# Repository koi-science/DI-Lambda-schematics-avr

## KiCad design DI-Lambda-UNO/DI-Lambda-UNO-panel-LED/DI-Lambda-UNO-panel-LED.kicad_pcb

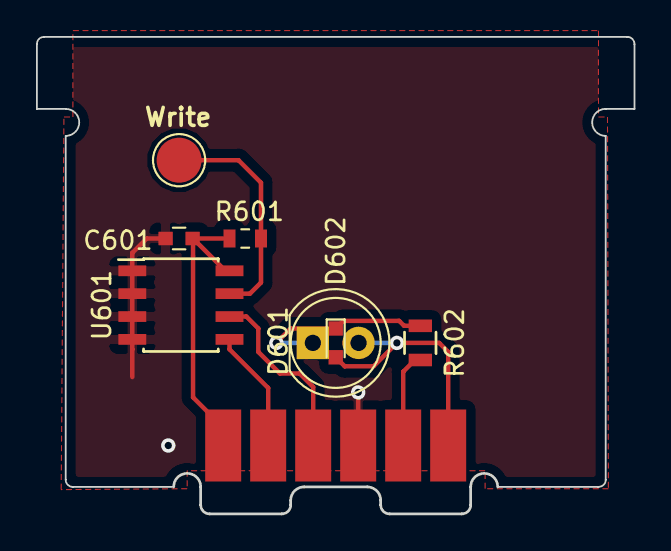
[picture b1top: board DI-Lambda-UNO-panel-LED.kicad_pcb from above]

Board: 2 copper layers, 33.2 x 26.5 mm, 9 parts (0 on the bottom side), 8 nets.

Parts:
C601: 0.1uF 25v; C_0603
D601: LED; LED_D5.0mm
D602: LED; LED_0603
J601: Conn_01X06; Contact-2.5x6
MK601: Mounting_Hole; Tab_LED
R601: 4.75K; R_0603_1608Metric
R602: 470R; R_0805
U601: 24LC02; SOIC-8_3.9x4.9mm_Pitch1.27mm
W601: WRITE; TestPoint_Pad_D2.5mm

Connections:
/GLED: J601.5, R602.1
/SCL: J601.3, U601.6
/SDA: J601.2, U601.5
/VCC: C601.1, J601.1, R601.1, U601.8
/VLED: D601.2, D602.2, J601.6
GND: C601.2, J601.4, U601.1, U601.2, U601.3, U601.4
unnamed: D601.1, D602.1, R602.2
unnamed: R601.2, U601.7, W601.1

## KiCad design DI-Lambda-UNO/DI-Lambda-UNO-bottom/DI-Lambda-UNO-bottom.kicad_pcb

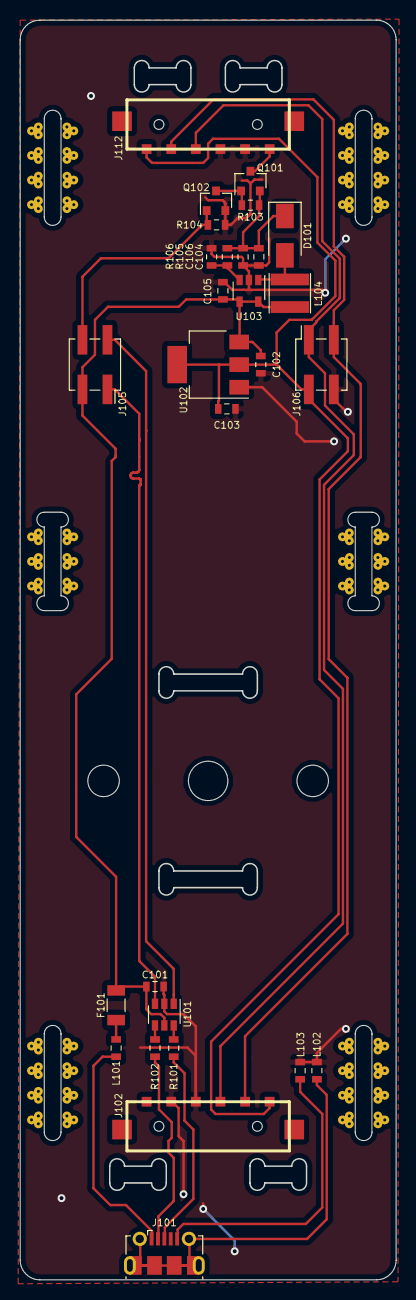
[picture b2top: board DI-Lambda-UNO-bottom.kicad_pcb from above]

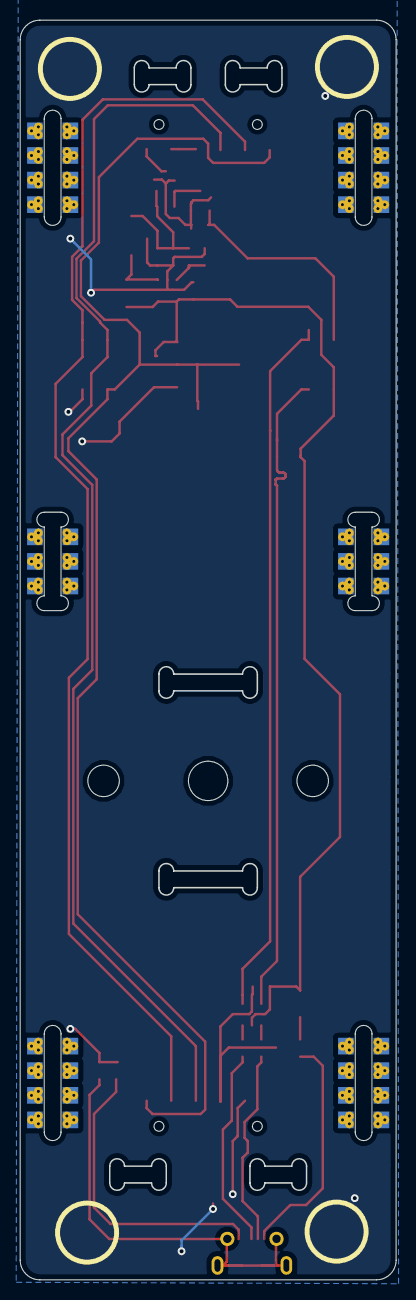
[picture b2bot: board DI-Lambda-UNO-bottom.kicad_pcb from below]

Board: 2 copper layers, 38.2 x 128.0 mm, 39 parts (6 on the bottom side), 21 nets.

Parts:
C101, C102, C103, C105: 4.7uF 6.3v; C_0603_1608Metric
C104, C106: 1uF 16v; C_0603_1608Metric
D101: SS14; D_SMA
F101: 0.2A; Fuse_1206_3216Metric
J101: USB_OTG; USB_Micro-B_Molex-105017-0001
J102, J112: CONN_01X06; Spring-contact-connector-2.5x6
J103, J104, J110, J111: Conn_02x04_Odd_Even; Pocket_1.6mm_10mm_no_cap_8pads_short_vias
J105, J106: Conn_02x02_Odd_Even; PinSocket_2x02_P2.54mm_Vertical_SMD
J107: Conn_01x01; Cuvette-holder
J108, J109: Conn_02x03_Odd_Even; Pocket_1.6mm_10mm_2cap_6pads_short_vias
L101, L102, L103: FB; L_0603_1608Metric
L104: 6.8uH; L_Taiyo-Yuden_NR-40xx
MK101: Mounting_Hole; Slot_LED
MK102, MK103: Mounting_Hole; Slot_pinhole
MK104: Mounting_Hole; Slot_sensor
Q101: AO3401; SOT-23
Q102: AO3400; SOT-23
R101, R102: 22R; R_0603_1608Metric
R103, R104, R106: 4.75k; R_0603_1608Metric
R105: 42.2k; R_0603_1608Metric
U101: USBLC6-2SC6; SOT-23-6
U102: 3.3v LDO; SOT-223-3_TabPin2
U103: AP3015; SOT-23-5

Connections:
/12v: C104.1, C106.1, D101.1, Q101.2, R103.1, R105.1
/DI_N: J101.2, R102.2
/DI_P: J101.3, R101.2
/D_N: J105.1, U101.3
/D_P: J105.2, U101.1
/LED_PWM: J105.4, Q102.1, R104.1
/SCL: J102.3, J106.1, J112.3
/SDA: J102.2, J106.3, J112.2
/SW: D101.2, L104.1, U103.1
/VBUS: C101.1, C102.2, C105.2, F101.1, J105.3, L104.2, U101.5, U102.3, U103.4, U103.5
/VCC: C103.2, J102.1, J106.2, J112.1, U102.2
/VLED: J112.6, Q101.3
/_D_N: R102.1, U101.4
/_D_P: R101.1, U101.6
GND: C101.2, C102.1, C103.1, C104.2, C105.1, C106.2, J102.4, J102.5, J106.4, J112.4, J112.5, L102.2, L103.2, Q102.2, R104.2, R106.2, U101.2, U102.1, U103.2
unnamed: F101.2, L101.1
unnamed: J101.1, L101.2
unnamed: J101.5, L103.1
unnamed: J101.6, L102.1
unnamed: Q101.1, Q102.3, R103.2
unnamed: R105.2, R106.1, U103.3

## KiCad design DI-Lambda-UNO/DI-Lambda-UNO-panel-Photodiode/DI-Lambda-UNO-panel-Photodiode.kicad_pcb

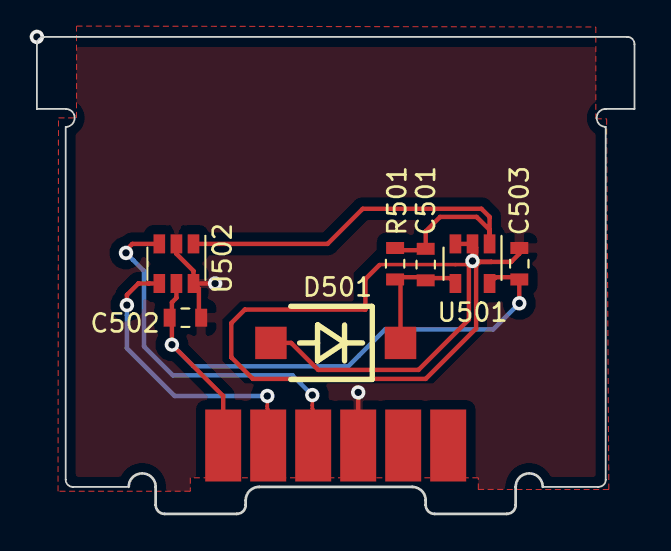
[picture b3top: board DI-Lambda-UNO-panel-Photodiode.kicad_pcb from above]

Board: 2 copper layers, 33.2 x 26.5 mm, 9 parts (0 on the bottom side), 6 nets.

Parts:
C501: 10pf; C_0603_1608Metric
C502, C503: 0.1uF 25v; C_0603_1608Metric
D501: D_Photo; 2-SMD-Everlight-Photodiode
J501: Conn_01X06; Contact-2.5x6
MK501: Mounting_Hole; Tab_SENSOR
R501: 1M; R_0603_1608Metric
U501: TP1271; SOT-23-5
U502: MCP3421A0T-E/CH; SOT-23-6

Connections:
/SCL: J501.3, U502.3
/SDA: J501.2, U502.4
/VCC: C502.1, C503.1, J501.1, U501.5, U502.5
GND: C502.2, C503.2, D501.2, J501.4, U501.2, U501.3, U502.2, U502.6
unnamed: C501.1, R501.1, U501.1, U502.1
unnamed: C501.2, D501.1, R501.2, U501.4

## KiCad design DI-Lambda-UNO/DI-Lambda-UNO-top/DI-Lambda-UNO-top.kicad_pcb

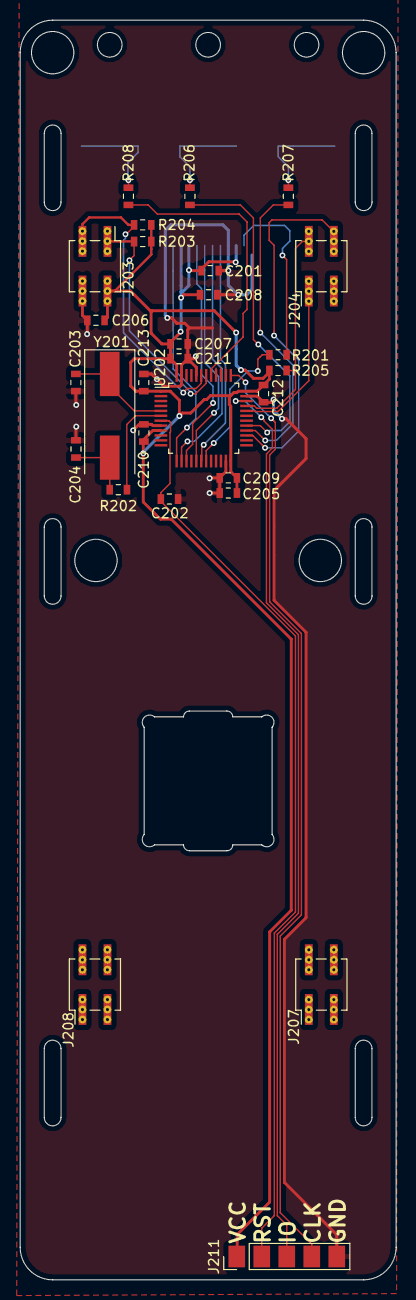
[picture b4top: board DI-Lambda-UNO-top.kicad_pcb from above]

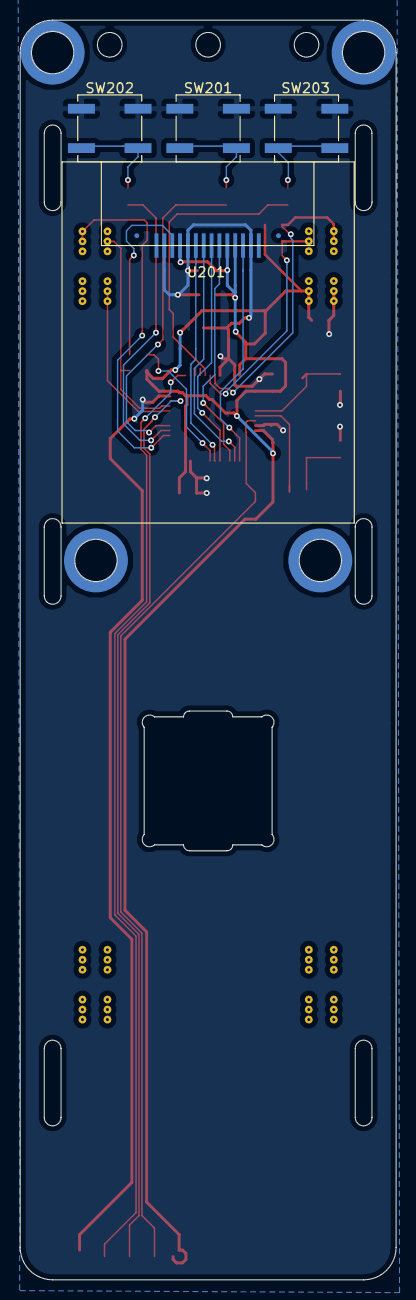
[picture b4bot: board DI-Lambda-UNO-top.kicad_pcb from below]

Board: 2 copper layers, 38.2 x 128.0 mm, 44 parts (14 on the bottom side), 26 nets.

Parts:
C201, C205, C206, C207: 4.7uF 6.3v; C_0603_1608Metric
C202, C208, C209, C210, C211, C212, C213: 0.1uF 25v; C_0603_1608Metric
C203, C204: 10pF 25V; C_0603_1608Metric
J201, J202, J209, J210: Conn_02x04_Odd_Even; Pocket_1.6mm_7mm_no_cap
J203, J204, J207, J208: Conn_02x02_Odd_Even; PinHeader_2x02_P2.54mm_Vertical_SMD_vias
J205, J206: Conn_02x03_Odd_Even; Pocket_1.6mm_7mm_no_cap
J211: Conn_01x05; Testpoint_1x05_P2.54mm_mixed
MK201: Mounting_Hole; Button_mounts_x3
MK202, MK203, MK204, MK205: Mounting_Hole; Mounting-Hole-SMT-nut-M3-4.3mm
MK206: Mounting_Hole; Cuvette-cutout-top
R201: 220R; R_0603_1608Metric
R202: 390R; R_0603_1608Metric
R203, R204: 4.75K; R_0603_1608Metric
R205, R206, R207, R208: 1.5K; R_0603_1608Metric
SW201: SW_SAMPLE; SW_SPST_B3SL-1002P
SW202: SW_MODE; SW_SPST_B3SL-1002P
SW203: SW_BLANK; SW_SPST_B3SL-1002P
U201: LCD_1.44_ST7735
U202: STM32F103C8Tx; LQFP-48_7x7mm_P0.5mm
Y201: 8Mhz; Crystal_SMD_HC49-SD

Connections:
/BLANK: R208.2, U202.41
/DN: J204.1, U202.32
/DP: J204.2, R205.2, U202.33
/LCD_A0: U201.7, U202.14
/LCD_CS: U201.12, U202.13
/LCD_LED: R201.2, U202.19
/LCD_RST: U201.6, U202.18
/LED_PWM: J204.4, U202.27
/MODE: R207.2, U202.28
/MOSI: U201.8, U202.17
/SAMPLE: R206.2, U202.29
/SCK: U201.9, U202.15
/SCL: J203.1, R203.2, U202.42
/SDA: J203.3, R204.1, U202.43
/SWDCLK: J211.4, U202.37
/SWDIO: J211.3, U202.34
/VCC: C201.2, C205.2, C206.2, C207.2, C208.1, C209.1, C210.1, C211.1, C212.1, C213.1, J203.2, J211.1, R203.1, R204.2, R205.1, U201.4, U201.10, U201.11, U202.1, U202.9, U202.24, U202.36, U202.48
/nRST: C202.1, J211.2, U202.7
GND: C201.1, C202.2, C203.2, C204.2, C205.1, C206.1, C207.1, C208.2, C209.2, C210.2, C211.2, C212.2, C213.2, J203.4, J211.5, SW201.2, SW202.2, SW203.2, U201.2, U201.5, U201.13, U202.8, U202.23, U202.35, U202.44, U202.47
unnamed: C203.1, U202.5, Y201.1
unnamed: C204.1, R202.2, Y201.2
unnamed: R201.1, U201.3
unnamed: R202.1, U202.6
unnamed: R206.1, SW201.1
unnamed: R207.1, SW202.1
unnamed: R208.1, SW203.1

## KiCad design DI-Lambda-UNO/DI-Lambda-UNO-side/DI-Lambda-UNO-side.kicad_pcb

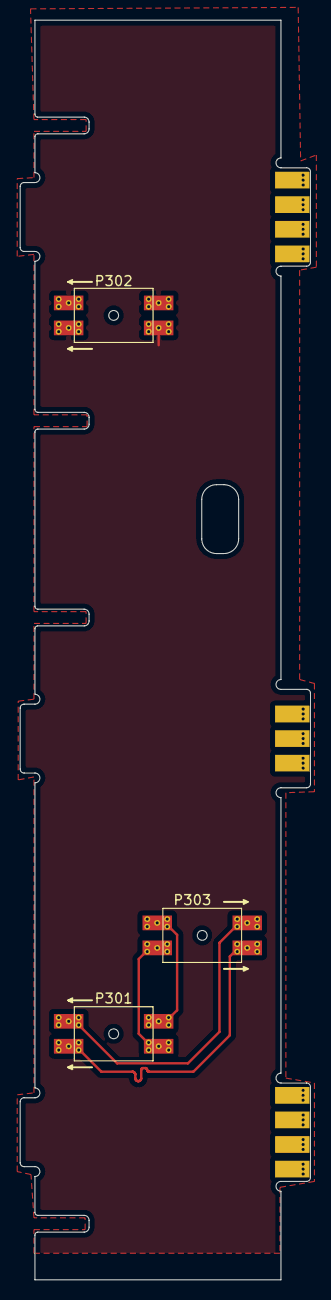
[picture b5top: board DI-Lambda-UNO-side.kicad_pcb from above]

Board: 2 copper layers, 29.5 x 128.0 mm, 10 parts (0 on the bottom side), 5 nets.

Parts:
MK301, MK302, MK303: Mounting_Hole; Tab_7mm_1.5mm
MK304: Mounting_Hole; Cuvette_holder_side_hole
P301, P302, P303: CONN_02X02; Female_socket_2.54_2x2p_horizontal_smt
P304, P306: CONN_01X04; Tab_10mm_4pads_vias_3mm
P305: CONN_01X04; Tab_10mm_3pads_vias_3mm

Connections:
/A+: P301.1, P303.3
/A-: P301.3, P303.1
/B+: P301.4, P303.2
/B-: P301.2, P303.4
GND: P302.1, P302.2, P302.3, P302.4

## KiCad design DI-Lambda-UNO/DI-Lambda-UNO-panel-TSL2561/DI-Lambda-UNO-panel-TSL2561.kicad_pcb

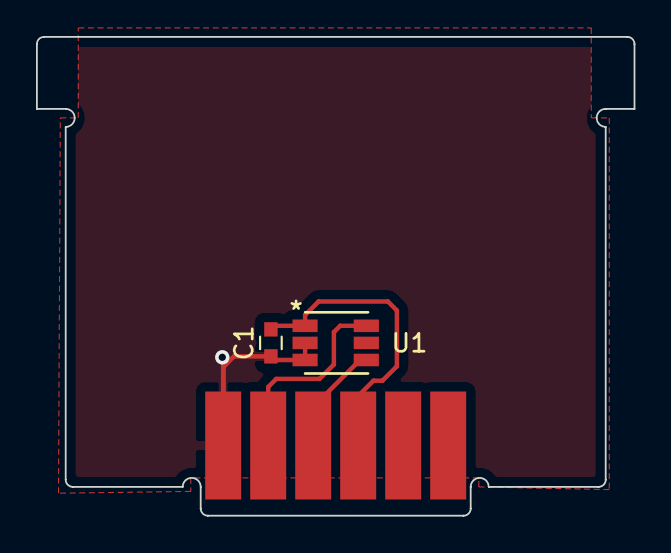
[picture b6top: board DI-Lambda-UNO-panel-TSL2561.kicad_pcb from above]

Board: 2 copper layers, 33.2 x 26.6 mm, 3 parts (0 on the bottom side), 4 nets.

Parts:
C1: C_Small; C_0603
J1: Conn_01X06; Contact-2.5x6
U1: TSL2561; TMB-6

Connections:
/SCL: J1.3, U1.4
/SDA: J1.2, U1.6
/VCC: C1.1, J1.4, U1.1
GND: C1.2, J1.1, U1.2, U1.3

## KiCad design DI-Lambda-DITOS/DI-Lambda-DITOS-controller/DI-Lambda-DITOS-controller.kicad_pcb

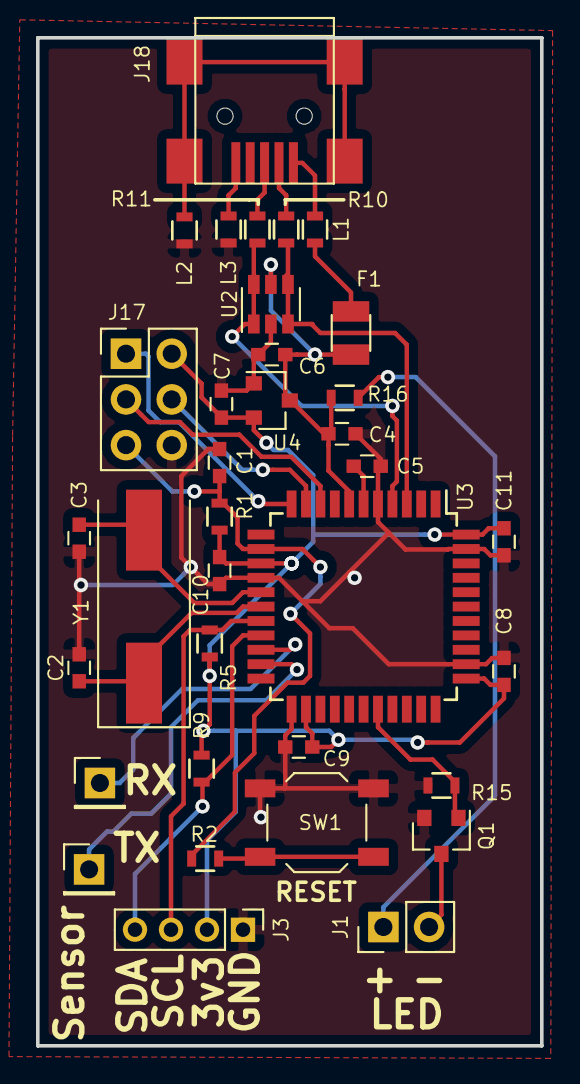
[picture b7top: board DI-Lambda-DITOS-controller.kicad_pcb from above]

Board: 2 copper layers, 28.0 x 56.0 mm, 35 parts (0 on the bottom side), 26 nets.

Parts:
C1: 0.1uF; C_0603
C2, C3: 22pF 25V; C_0603
C4: 4.7uF 25V; C_0603
C5: 1uF 25V; C_0603
C6, C7: 4.7uF 25v; C_0603
C8, C9, C10, C11: 0.1uF 25v; C_0603
F1: 0.2A; Fuse_SMD1206_Reflow
J1: Conn_01x02; Pin_Header_Straight_1x02_Pitch2.54mm
J2, J4: Conn_01X01; Pin_Header_Straight_1x01_Pitch2.54mm
J3: Conn_01x04; Pin_Header_Straight_1x04_Pitch2.00mm
J17: CONN_02X03; Pin_Header_Straight_2x03_Pitch2.54mm
J18: USB_OTG; USB_Mini-B
L1, L2, L3: FB; R_0603
Q1: AO3400; SOT-23
R1, R5, R9, R15: 4.7k; R_0603
R2: 330R; R_0603
R10, R11: 22R; R_0603
R16: DNP; R_0603
SW1: RESET; SW_SPST_TL3342
U2: USBLC6-2SC6; SOT-23-6
U3: ATMEGA32U4-MU; TQFP-44_10x10mm_Pitch0.8mm
U4: 3.3v LDO; SOT-23
Y1: 8Mhz; Crystal_SMD_HC49-SD

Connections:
/GLED: J1.2, Q1.3
/LED_PWM: Q1.1, R15.1, U3.29
/MISO: J17.1, U3.11
/MOSI: J17.4, U3.10
/RST: C1.2, J17.5, R1.2, R2.1, U3.13
/RX: J2.1, U3.20
/SCK: J17.3, U3.9
/SCL: J3.3, R5.2, U3.18
/SDA: J3.4, R9.1, U3.19
/TX: J4.1, U3.21
/VBUS: C4.1, C6.2, F1.1, R16.1, U2.5, U3.7, U4.3
/VCC: C7.2, C8.1, C9.1, C10.1, C11.1, J3.2, J17.2, R1.1, R5.1, R9.2, U3.14, U3.24, U3.34, U3.44, U4.2
/VLED: J1.1, R16.2
GND: C1.1, C2.2, C3.2, C4.2, C5.2, C6.1, C7.1, C8.2, C9.2, C10.2, C11.2, J3.1, J17.6, L2.2, L3.2, Q1.2, R15.2, SW1.1, U2.2, U3.5, U3.15, U3.23, U3.35, U3.43, U4.1
unnamed: C2.1, U3.17, Y1.1
unnamed: C3.1, U3.16, Y1.2
unnamed: C5.1, U3.6
unnamed: F1.2, L1.1
unnamed: J18.1, L1.2
unnamed: J18.2, R10.2
unnamed: J18.3, R11.2
unnamed: J18.5, L3.1
unnamed: J18.6, L2.1
unnamed: R2.2, SW1.2
unnamed: R10.1, U2.3, U2.4, U3.3
unnamed: R11.1, U2.1, U2.6, U3.4

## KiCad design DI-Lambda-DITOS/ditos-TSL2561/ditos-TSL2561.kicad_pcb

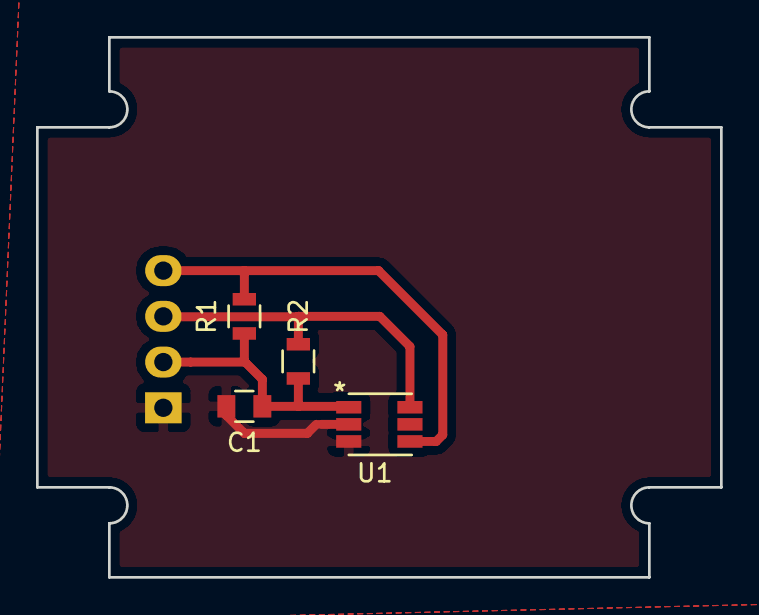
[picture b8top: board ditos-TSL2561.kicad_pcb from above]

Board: 2 copper layers, 38.0 x 30.0 mm, 5 parts (1 on the bottom side), 4 nets.

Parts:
C1: 1uF; C_0805
P1: CONN_01X04; Pin_Header_Straight_1x04
R1, R2: 4K7; R_0805
U1: TSL2561; TMB-6

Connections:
GND: C1.1, P1.1, U1.2, U1.3
unnamed: P1.3, R2.1, U1.6
unnamed: P1.4, R1.2, U1.4
VCC: C1.2, P1.2, R1.1, R2.2, U1.1

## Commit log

2017-08-27 Import DI-Lambda DITOS schematics
2017-08-27 Import DI-Lambda UNO v1.0
2017-08-27 Fix DI-Lambda DITOS controller library references
2017-08-27 Fix DI-Lambda DITOS LED module library references
2017-08-27 Fix DI-Lambda DITOS TSL2561 module library references
2017-08-27 DI-Lambda UNO bottom cleanup
2017-08-27 DI-Lambda UNO insert cleanup
2017-08-27 Fix spring contact module name
2017-08-27 DI-Lambda UNO LED module cleanup
2017-08-27 DI-Lambda UNO TSL2561 modules cleanup
2017-08-27 Move the TSL2561 lib into the libs directory
2017-08-27 DI-Lambda UNO side panel cleanup
2017-08-27 DI-Lambda UNO top panel cleanup
2017-08-27 Add CC-BY-SA 4.0 lisence
2017-10-23 Use longer contact pas for the spring connector
2017-10-23 Remove notches from the LED/Sensor/Pinhole panels
2017-10-23 Swap SDA/SCL on the main board
2017-10-23 Connect UCAP to VCC on the main board
2017-10-23 Increase cuvette holder hole size to 13mm
2017-10-23 Increase top plate cuvette hole size to 13mm
2017-10-23 Remove connectors and notches from the side panels
2017-10-23 Rework the top plate - STM+THT connectors and new dimensions
2017-10-23 Update connectors on the bottom plate
2017-10-23 Fix pinhole plate tab size, 13mm
2017-10-23 Move spring connectors 0.3mm back on the bottom plate
2017-10-23 Fix up the routing after connector update on the bottom plate
2017-10-23 Update main plate dimensions
2017-10-23 Use SMT pin header for ISP on the bottom plate
2017-10-23 Pour copper everywhere on the main plate
2017-10-23 Clean up routing, a bit shielding behind the crystal on bottom plate
2017-10-23 Clean up silkscreen, use SMT pads for RX/TX on the main plate
2017-10-23 Use Micro-USB instead on Mini on the bottom plate
2017-10-25 Change pinhole tab length to 15mm
2017-10-25 Copper pour on the LED board
2017-10-25 Copper pour and slight dimension adjusements on the TSL5261 board
2017-10-25 Copper pour on the side boards
2017-10-25 Adjust connctors on the cuvette holder
2017-11-02 Fill in a few component names on the bottom board
2017-11-02 Fix up connector footprints on the cuvette holder board
2017-11-26 Adjust copper pour on multiple boards
2017-12-02 Add a photodiode-based sensor board
2017-12-05 Photodiode board: Fix the op amp pinout
2017-12-05 Photodiode board: Add missing libs and footprints
2017-12-05 Photodiode board: Convert to 18mm height
2017-12-05 Pinhole board: Convert to 18mm height
2017-12-08 LED board: convert to 18mm height
2017-12-08 Side board: Convert to 18mm height
2017-12-14 Add the cuvette holder footprint
2017-12-14 Add the 2x2p horizontal 2.54mm SMT socket footprint
2018-02-03 Version 1.5 redesign WIP
2018-03-10 Version 1.5
2018-04-01 Version 1.6
2018-04-01 Add missing footprints
2019-07-14 More missing fotprints
